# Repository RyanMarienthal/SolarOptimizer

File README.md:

This project contains the design of a solar power optimizer.

The project was designed in KiCad, and the files are provided and can be edited to the users demands.

The project has generic values for R1, R2, R3, and R4 because they are intended to be chosen by the user depending on the voltage of the system.

Standard divider sizes are shown below:
  48V OCV: R1 = 40kOhm, R2 = 7500Ohm, R3 = 1000Ohm, R4 = 2000Ohm
  R1 and R2 must be rated for at least 1/8 Watt.
  R3 and R4 must be rated for at least 1 Watt.

  24V OCV: R1 = 16kOhm, R2 = 2000Ohm, R3 = Short, R4 = Open
  R1 and R2 must be rated for at least 1/8 Watt

  20V OCV: R1 = 12500, R2 = 7500, R3 = Short, R4 = Open

  500V OCV: R1 = 430K, R2 = 8000, R4 = 2000
            There are 3 slots for R3 (labelled R3_P1, R3_P2, R3_P3) which are in parallel
            Two of these should be a 7W 50K resistor in parallel with a 5W 62K Resistor
            The third slot should be one 5W 62K resistor

Production files are aslo included, the zip file and BOM are formatted for JLCPCB manufacturing and assembly.

If another software is used, these may need to be altered.

ORDERING INSRUCTIONS:
  Navigate to SolarOptimizer Git Upload\production and download SolarOptimizer3.0.zip

  This file can be uploaded directly to a PCB manufacturer and ordered

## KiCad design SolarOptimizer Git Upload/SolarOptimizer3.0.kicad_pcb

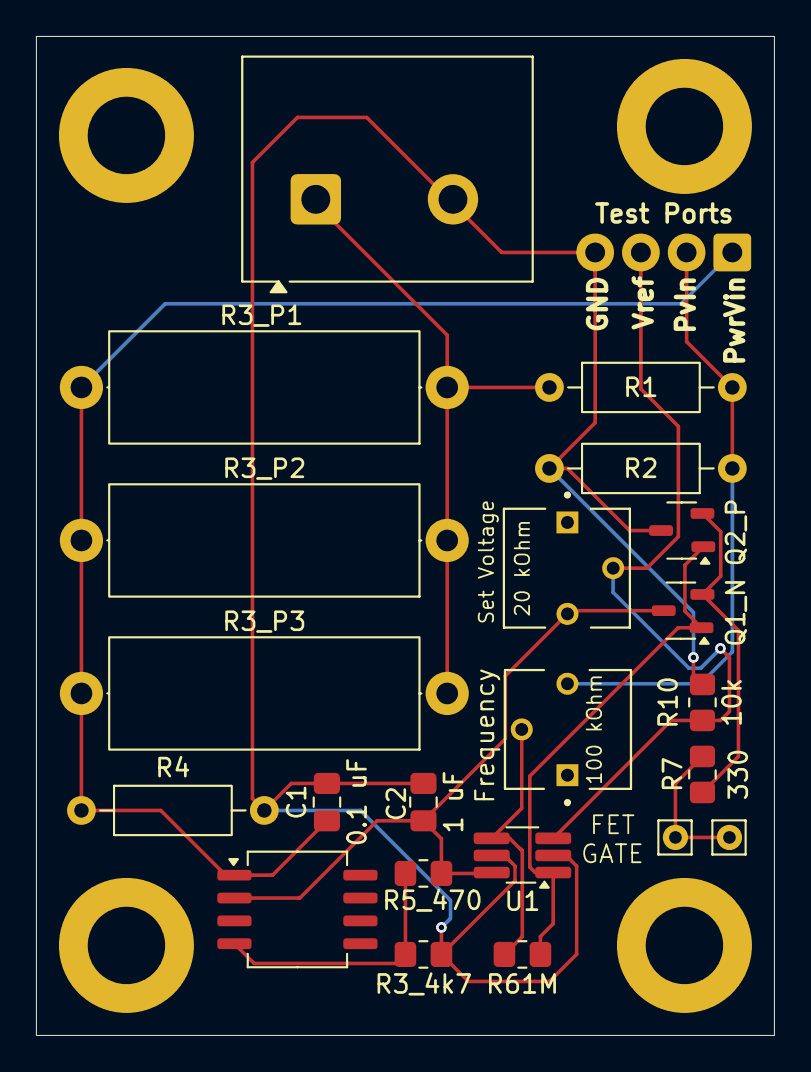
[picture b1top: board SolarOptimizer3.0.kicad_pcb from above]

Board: 2 copper layers, 41.0 x 55.5 mm, 27 parts (0 on the bottom side), 11 nets.

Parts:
C1: 0.1 uF; C_0805_2012Metric_Pad1.18x1.45mm_HandSolder
C2: 1 uF; C_0805_2012Metric_Pad1.18x1.45mm_HandSolder
H3, H4, H5, H6: MountingHole; MountingHole_4.3mm_M4_DIN965_Pad
J1, J3: Pin_D0.7mm_L6.5mm_W1.8mm_FlatFork
J2: Screw_Terminal_01x02; TerminalBlock_gauge 10
J5: Screw_Terminal_01x04; 4Pin_Terminal_NoSilk
Q1_N: N-Channel; SOT-23-3
Q2_P: P-Channel; SOT-23-3
R1, R2, R4: R; R_Axial_DIN0207_L6.3mm_D2.5mm_P10.16mm_Horizontal
R3_4k7: 4k7; R_0805_2012Metric_Pad1.20x1.40mm_HandSolder
R3_P1, R3_P2, R3_P3: R; R_Axial_DIN0617_L17.0mm_D6.0mm_P20.32mm_Horizontal
R5_470: 470; R_0805_2012Metric_Pad1.20x1.40mm_HandSolder
R7: 330; R_0805_2012Metric_Pad1.20x1.40mm_HandSolder
R10: 10k; R_0805_2012Metric_Pad1.20x1.40mm_HandSolder
R61M: 1 MOhm; R_0805_2012Metric_Pad1.20x1.40mm_HandSolder
Rp1: 20 kOhm; TRIM_3362P-1-253LF
Rp3: 100 kOhm; TRIM_3362P-1-253LF
U1: TLV1805DBVR; TSOT-23-6_HandSoldering
U2: LM317LCDR; SOIC-8_5.3x6.2mm_P1.27mm

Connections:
+CompIn: R61M.2, Rp3.2, U1.4 (IN+)
/HVDC Line: J2.1, R1.1, R3_P1.1, R3_P2.1, R3_P3.1
CompOut: Q1_N.1 (G), Q2_P.1 (G), R61M.1, U1.1 (OUT)
GND: C1.2, C2.2, J2.2, J5.4, Q2_P.2 (D), R2.2, R3_4k7.1, R4.2, R10.2, U1.2 (V-), U1.5 (SD)
unnamed: J1.1, J3.1, R7.2
unnamed: Q1_N.3 (S), Q2_P.3 (S), R7.1
unnamed: R3_4k7.2, R5_470.2, U2.4 (ADJUSTMENT)
PV Input: J5.2, R1.2, R2.1, Rp3.3
RefIn: J5.3, R10.1, Rp1.2, U1.3 (IN-)
RegIn: C1.1, J5.1, R3_P1.2, R3_P2.2, R3_P3.2, R4.1, U2.1 (IN)
RegOut: C2.1, Q1_N.2 (D), R5_470.1, Rp1.3, U1.6 (V+), U2.2 (OUT)

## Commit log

2025-09-17 Add files via upload
    Uploaded Kicad Files and JLC Production files
2025-09-17 Optimizer Instructions.md
